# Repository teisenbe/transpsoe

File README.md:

# Transpsoe

This is a Eurorack 1u 22hp module that performs pitch transposition on V/oct signals. Outputs are accurate to within 1.5mV, often better. The panel is designed for Intellijel 1u, but is (untested) compatible with Pulp Logic 1u. Build instructions can be found [here](build_instructions.md). **Note: revs 1 and 2 have not been built yet. Rev 1 but is only minor changes from rev 0, but 2 is more substantial. See the [changelog](CHANGELOG.md) for details.**

## Project Status

- [x] Complete initial CAD work
- [x] SPICE simulations
- [x] Order test board to verify footprints, board alignment, and power connector clearance
- [x] Order and assemble rev 0 PCBs and components
- [ ] Order and assemble rev 2 PCBs and components

## Known issues
- Something on channel 1 produces around -0.5 to -1mV of error in a way that is visible on the +S output (and all channel 2 outputs when summing is enabled). It does not seem to show up on the other outputs, but this might just mean its calibrated out of the voltage refs.

## Controls

Transpsoe has two inputs, 8 outputs, a toggle switch, and a rotary knob. The two rows of jacks corresponds roughly to two channels of operation.

### Inputs

The inputs are identified by white outlines. The jacks are both normed to 0V. Each input is fed to the jacks to their right. The channel summing mechanism can also feed the top input downward.

### Channel summing

The toggle switch can be used to bridge the two channels. If the toggle switch is in the down position, pointing toward the "ADD" label, then the bottom outputs behaves as if the bottom input is increased by the top input and the semitone transposition.

### Semitone transpostion

The rotary knob selects semitone transposition in 12-TET. 0 semitones corresponds to the vertical position, with the extra long radial line.  The number of semitones increases by 1 as you move clockwise. Semitone transposition applies only to the first channel unless channel summing is enabled.

### Outputs

Each output is labeled with an integer representing a number of octaves to shift up the channel's input by. The top channel is also shifted up by the number of semitones selected on the knob.

## Technical details

### Power consumption

- 12V: ~13 mA
- -12V: ~13 mA

### Input/Output voltage limits

All inputs should function fine in the +/- 11V range. All outputs should function fine as long as their expected value is in the +/- 11V range.

### Calibration

1. Apply power to the module.
2. Unplug any patch cables, set the semitone knob to 0, and the summing switch to the off position.
3. Measure the first output on the top. It should be 0V, +/- 1.5mV. This is not adjustable. A substantially different value is indicative of a problem with the circuit.
4. Measure the second output on the top. It should be 1V. Adjust trimpot RV1 to get it as close as possible to 1V.
5. Measure the third and fourth outputs on the top and the first on the bottom. They should be 2V, 3V, and -1V, respectively. They should be pretty close at this point, but if they're not, you can further tune RV1 to minimize the error across the -1V, 1V, 2V, and 3V values.
6. Set the semitone knob to 1 and the summing switch to the off position.
7. Measure the first output on the top. It should be 83.33mV (1/12 mV). Adjust trimpot RV2 to tune as close to 83.33mV as you can, since any error here is going to be multiplied by up to 11.

### Voltage reference

The circuit generates a 4.096V +/- 0.1% reference using a shunt diode. A resistor divider with a trimpot is used to get a 4V reference. -1V, 1V, 2V, and 3V references are generated from the 4V reference.

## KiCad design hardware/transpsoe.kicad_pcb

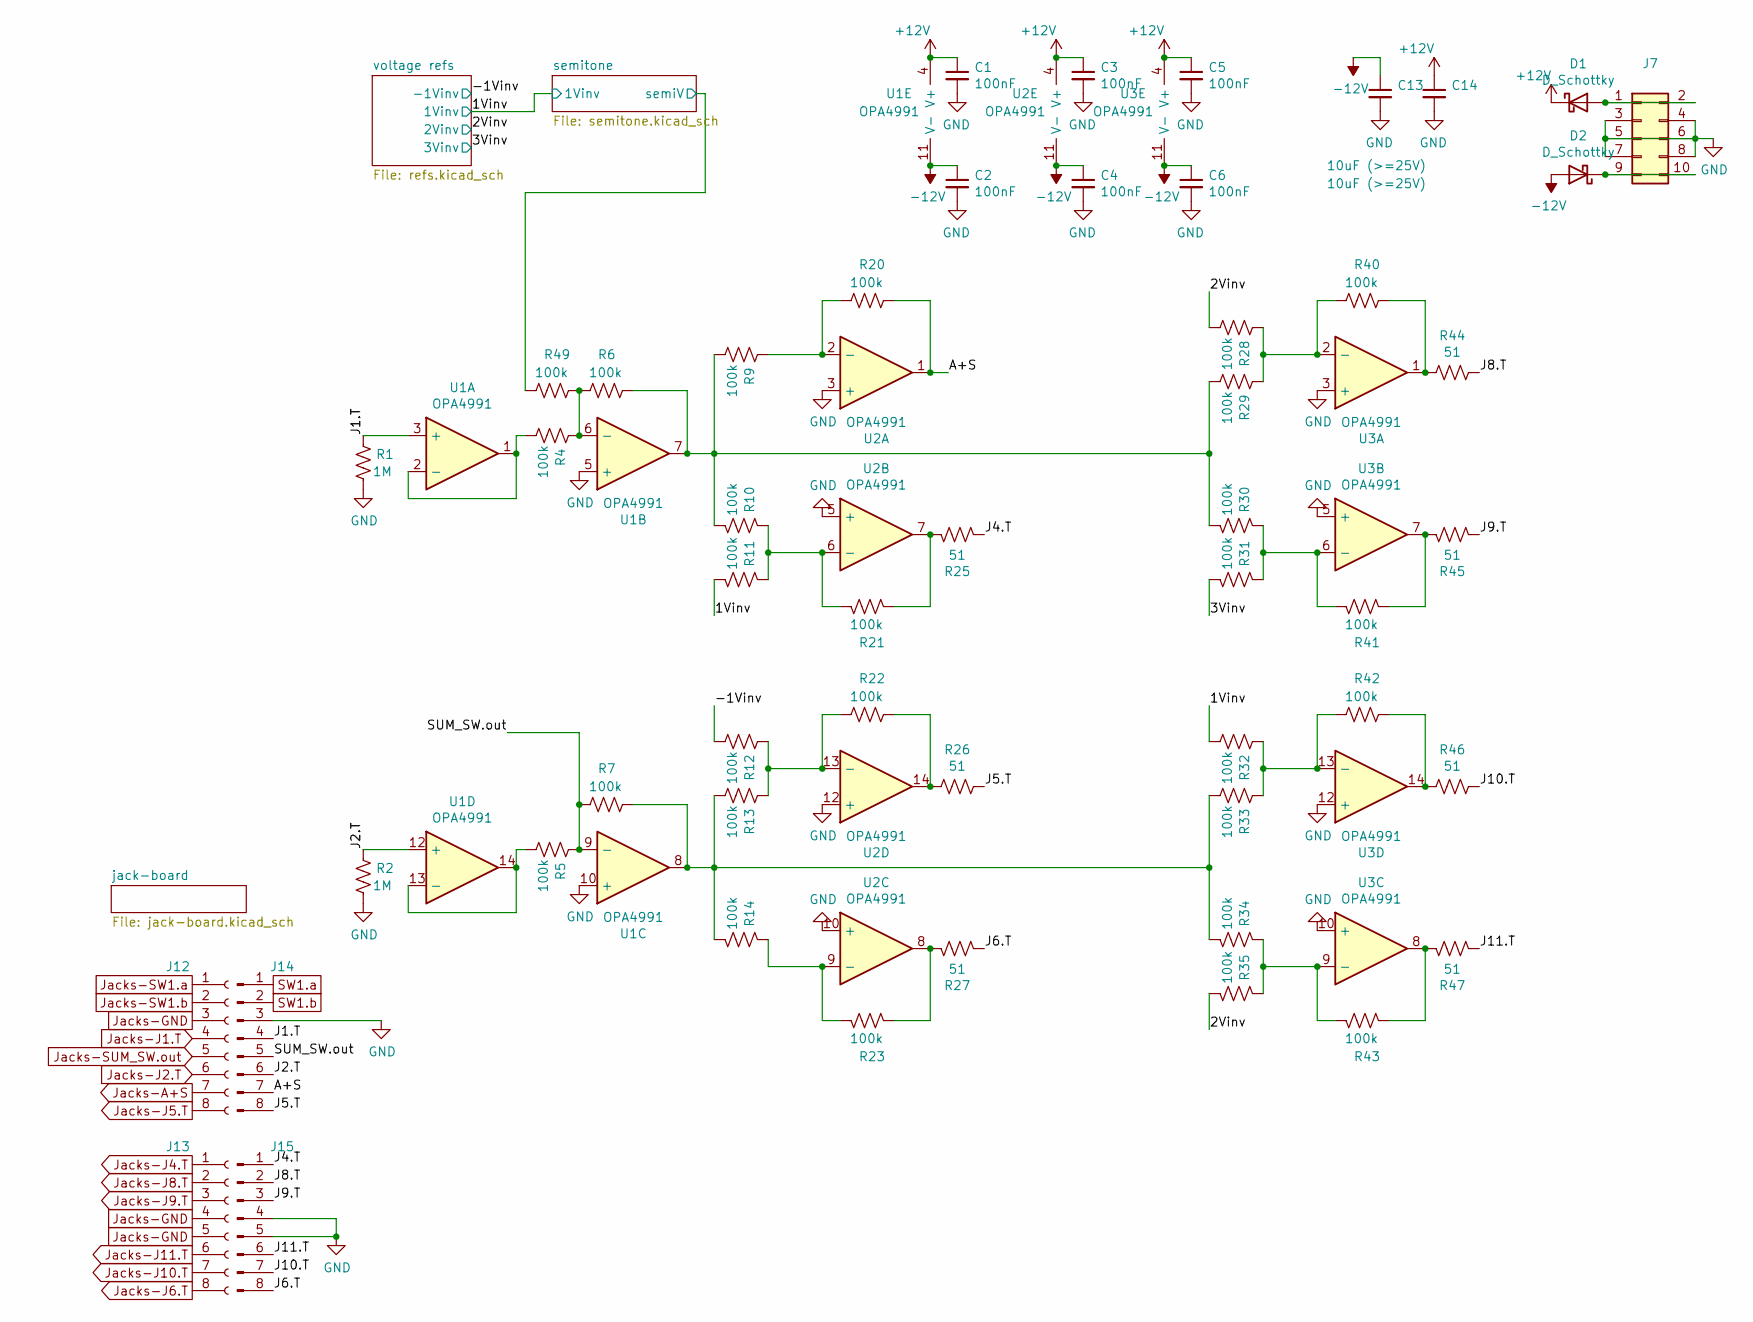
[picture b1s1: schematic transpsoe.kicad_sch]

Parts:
C1, C2, C3, C4, C5, C6: 100nF; C_0603_1608Metric_Pad1.08x0.95mm_HandSolder
C13, C14: 10uF (>=25V); C_0603_1608Metric_Pad1.08x0.95mm_HandSolder
D1, D2: D_Schottky; D_SMA_Handsoldering
J7: Conn_02x05_Odd_Even; PinHeader_2x05_P2.54mm_Vertical
J12, J13: Conn_01x08_Female; SAMTEC_SSM-108-L-SV-LC
J14, J15: Conn_01x08_Male; SAMTEC_TSM-108-01-F-SV-LC
R1, R2: 1M; R_0603_1608Metric_Pad0.98x0.95mm_HandSolder; Tolerance 5%
R4, R5, R6, R7, R9, R10, R11, R12, R13, R14, R20, R21, R22, R23, R28, R29, R30, R31, R32, R33, R34, R35, R40, R41, R42, R43, R49: 100k; R_0603_1608Metric_Pad0.98x0.95mm_HandSolder; Tolerance 0.1%
R25, R26, R27, R44, R45, R46, R47: 51; R_0603_1608Metric_Pad0.98x0.95mm_HandSolder; Tolerance 5%
U1, U2, U3: OPA4991; SOIC-14_3.9x8.7mm_P1.27mm

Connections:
+12V: C1.1, C3.1, C5.1, C14.1, D1.1 (K), U1.4 (V+), U2.4 (V+), U3.4 (V+); also elsewhere on the board
-12V: C2.1, C4.1, C6.1, C13.1, D2.2 (A), U1.11 (V-), U2.11 (V-), U3.11 (V-); also elsewhere on the board
/1Vinv: R11.2, R32.2; also elsewhere on the board
/2Vinv: R28.2, R35.2; also elsewhere on the board
/3Vinv: R31.2; also elsewhere on the board
/-1Vinv: R12.2; also elsewhere on the board
/A+S: J14.7, R20.1, U2.1
/J1.T: J14.4, R1.1, U1.3 (+)
/J2.T: J14.6, R2.1, U1.12 (+)
/J4.T: J15.1, R25.2
/J5.T: J14.8, R26.2
/J6.T: J15.8, R27.2
/J8.T: J15.2, R44.2
/J9.T: J15.3, R45.2
/J10.T: J15.7, R46.2
/J11.T: J15.6, R47.2
/SUM_SW.out: J14.5, R5.1, R7.2, U1.9 (-)
GND: C1.2, C2.2, C3.2, C4.2, C5.2, C6.2, C13.2, C14.2, J7.3, J7.4, J7.5, J7.6, J7.7, J7.8, J14.3, J15.4, J15.5, R1.2, R2.2, U1.5 (+), U1.10 (+), U2.3 (+), U2.5 (+), U2.10 (+), U2.12 (+), U3.3 (+), U3.5 (+), U3.10 (+), U3.12 (+); also elsewhere on the board
Jacks-A+S: J12.7; also elsewhere on the board
Jacks-GND: J12.3, J13.4, J13.5; also elsewhere on the board
Jacks-J1.T: J12.4; also elsewhere on the board
Jacks-J2.T: J12.6; also elsewhere on the board
Jacks-J4.T: J13.1; also elsewhere on the board
Jacks-J5.T: J12.8; also elsewhere on the board
Jacks-J6.T: J13.8; also elsewhere on the board
Jacks-J8.T: J13.2; also elsewhere on the board
Jacks-J9.T: J13.3; also elsewhere on the board
Jacks-J10.T: J13.7; also elsewhere on the board
Jacks-J11.T: J13.6; also elsewhere on the board
Jacks-SUM_SW.out: J12.5; also elsewhere on the board
Jacks-SW1.a: J12.1; also elsewhere on the board
Jacks-SW1.b: J12.2; also elsewhere on the board
unnamed: D1.2 (A), J7.1, J7.2
unnamed: D2.1 (K), J7.9, J7.10
unnamed: R4.1, R6.2, R49.1, U1.6 (-)
unnamed: R4.2, U1.1, U1.2 (-)
unnamed: R5.2, U1.13 (-), U1.14
unnamed: R10.1, R11.1, R21.2, U2.6 (-)
unnamed: R6.1, R9.2, R10.2, R29.2, R30.2, U1.7
unnamed: R12.1, R13.1, R22.2, U2.13 (-)
unnamed: R7.1, R13.2, R14.2, R33.2, R34.2, U1.8
unnamed: R14.1, R23.2, U2.9 (-)
unnamed: R9.1, R20.2, U2.2 (-)
unnamed: R21.1, R25.1, U2.7
unnamed: R22.1, R26.1, U2.14
unnamed: R23.1, R27.1, U2.8
unnamed: R28.1, R29.1, R40.2, U3.2 (-)
unnamed: R30.1, R31.1, R41.2, U3.6 (-)
unnamed: R32.1, R33.1, R42.2, U3.13 (-)
unnamed: R34.1, R35.1, R43.2, U3.9 (-)
unnamed: R40.1, R44.1, U3.1
unnamed: R41.1, R45.1, U3.7
unnamed: R42.1, R46.1, U3.14
unnamed: R43.1, R47.1, U3.8
SW1.a: J14.1; also elsewhere on the board
SW1.b: J14.2, R49.2; also elsewhere on the board

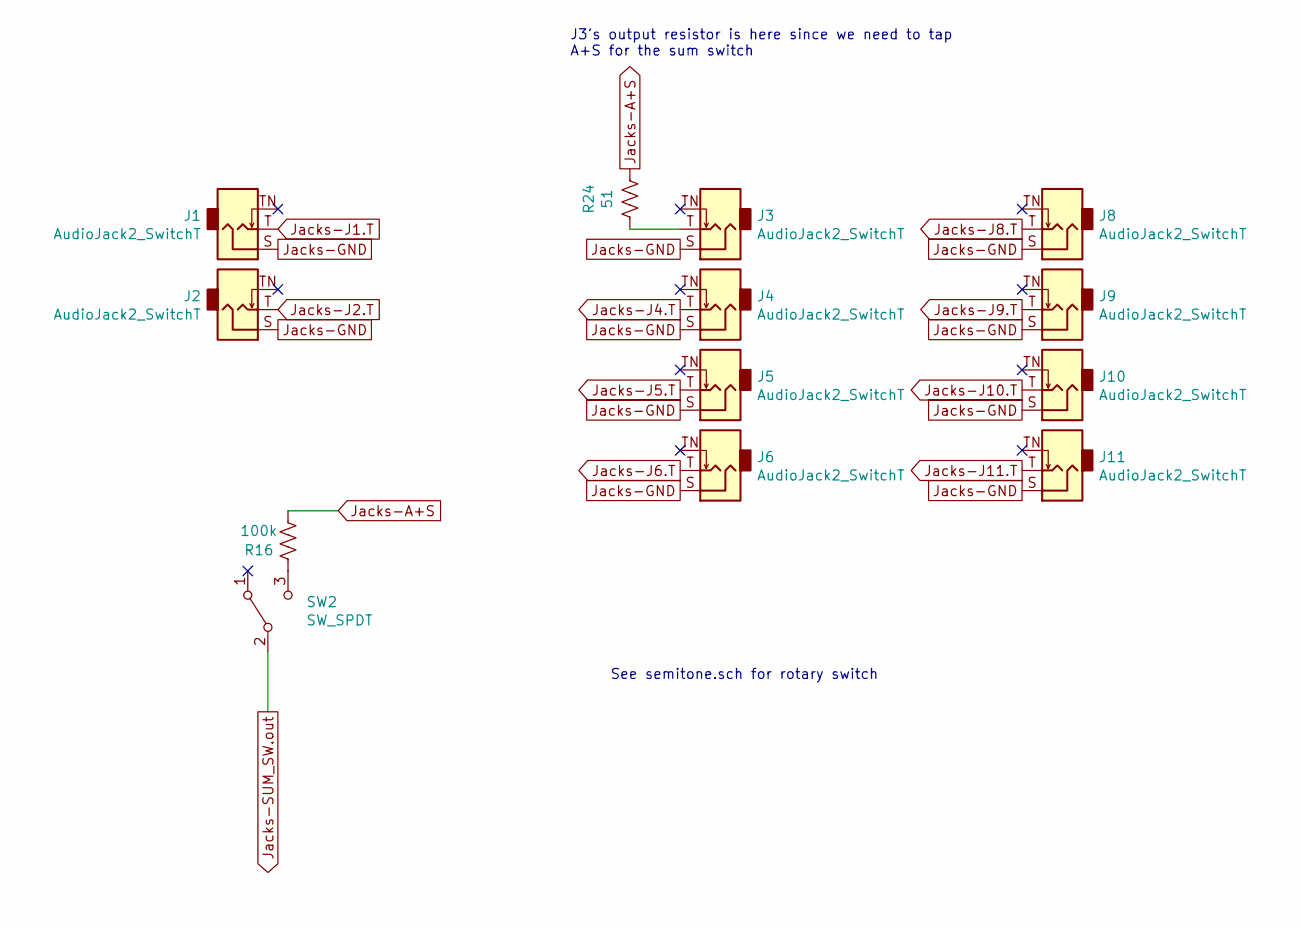
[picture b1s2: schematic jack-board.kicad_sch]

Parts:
J1, J2, J3, J4, J5, J6, J8, J9, J10, J11: AudioJack2_SwitchT; PJ-301BM
R16: 100k; R_0603_1608Metric_Pad0.98x0.95mm_HandSolder; Tolerance 0.1%
R24: 51; R_0603_1608Metric_Pad0.98x0.95mm_HandSolder; Tolerance 5%
SW2: SW_SPDT; BNT11SEA5QE

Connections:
Jacks-A+S: R16.2, R24.2; also elsewhere on the board
Jacks-GND: J1.S, J2.S, J3.S, J4.S, J5.S, J6.S, J8.S, J9.S, J10.S, J11.S; also elsewhere on the board
Jacks-J1.T: J1.T; also elsewhere on the board
Jacks-J2.T: J2.T; also elsewhere on the board
Jacks-J4.T: J4.T; also elsewhere on the board
Jacks-J5.T: J5.T; also elsewhere on the board
Jacks-J6.T: J6.T; also elsewhere on the board
Jacks-J8.T: J8.T; also elsewhere on the board
Jacks-J9.T: J9.T; also elsewhere on the board
Jacks-J10.T: J10.T; also elsewhere on the board
Jacks-J11.T: J11.T; also elsewhere on the board
Jacks-SUM_SW.out: SW2.2 (B); also elsewhere on the board
unnamed: J3.T, R24.1
unnamed: R16.1, SW2.3 (C)

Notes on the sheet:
See semitone.sch for rotary switch
J3's output resistor is here since we need to tap A+S for the sum switch

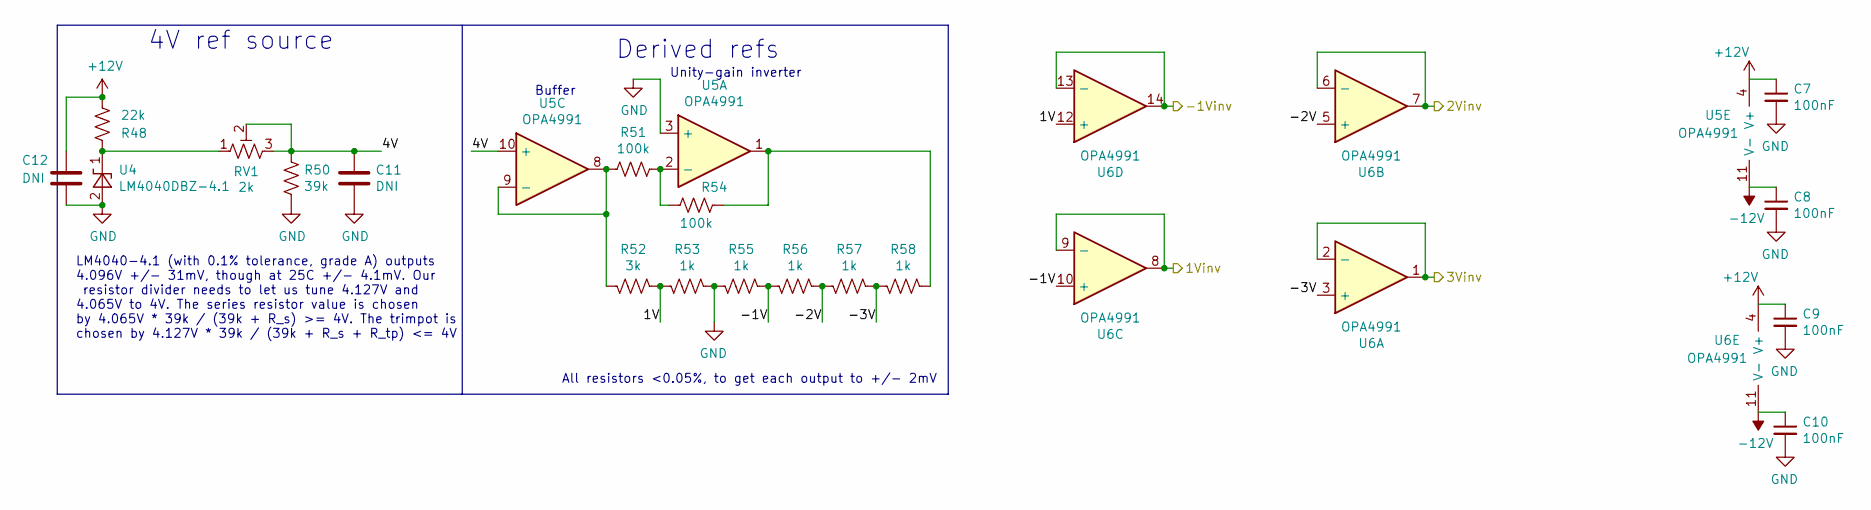
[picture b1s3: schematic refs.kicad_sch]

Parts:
C7, C8, C9, C10: 100nF; C_0603_1608Metric_Pad1.08x0.95mm_HandSolder
C11, C12: DNI; C_0603_1608Metric_Pad1.08x0.95mm_HandSolder
R48: 22k; R_0603_1608Metric_Pad0.98x0.95mm_HandSolder; Tolerance 1%
R50: 39k; R_0603_1608Metric_Pad0.98x0.95mm_HandSolder; Tolerance 1%, but low temp co
R51, R54: 100k; R_0603_1608Metric_Pad0.98x0.95mm_HandSolder; Tolerance 0.1%
R52: 3k; R_0603_1608Metric_Pad0.98x0.95mm_HandSolder; Tolerance 0.05%, low temp co
R53, R55, R56, R57, R58: 1k; R_0603_1608Metric_Pad0.98x0.95mm_HandSolder; Tolerance 0.05%, low temp co
RV1: 2k; Potentiometer_Bourns_3296W_Vertical; Tolerance 10%
U4: LM4040DBZ-4.1; SOT-23; Tolerance 0.1%
U5, U6: OPA4991; SOIC-14_3.9x8.7mm_P1.27mm

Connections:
+12V: C7.1, C9.1, C12.1, R48.1, U5.4 (V+), U6.4 (V+); also elsewhere on the board
-12V: C8.1, C10.1, U5.11 (V-), U6.11 (V-); also elsewhere on the board
/1Vinv: U6.8, U6.9 (-); also elsewhere on the board
/2Vinv: U6.6 (-), U6.7; also elsewhere on the board
/3Vinv: U6.1, U6.2 (-); also elsewhere on the board
/-1Vinv: U6.13 (-), U6.14; also elsewhere on the board
/voltage refs/1V: R52.2, R53.1, U6.12 (+)
/voltage refs/4V: C11.1, R50.1, RV1.2, RV1.3, U5.10 (+)
/voltage refs/-1V: R55.2, R56.1, U6.10 (+)
/voltage refs/-2V: R56.2, R57.1, U6.5 (+)
/voltage refs/-3V: R57.2, R58.1, U6.3 (+)
GND: C7.2, C8.2, C9.2, C10.2, C11.2, C12.2, R50.2, R53.2, R55.1, U4.2 (A), U5.3 (+); also elsewhere on the board
unnamed: R48.2, RV1.1, U4.1 (K)
unnamed: R51.1, R54.2, U5.2 (-)
unnamed: R51.2, R52.1, U5.8, U5.9 (-)
unnamed: R54.1, R58.2, U5.1

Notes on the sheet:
Derived refs
Unity-gain inverter
All resistors <0.05%, to get each output to +/- 2mV
4V ref source
LM4040-4.1 (with 0.1% tolerance, grade A) outputs 4.096V +/- 31mV, though at 25C +/- 4.1mV. Our resistor divider needs to let us tune 4.127V and 4.065V to 4V. The series resistor value is chosen by 4.065V * 39k / (39k + R_s) >= 4V. The trimpot is chosen by 4.127V * 39k / (39k + R_s + R_tp) <= 4V
Buffer

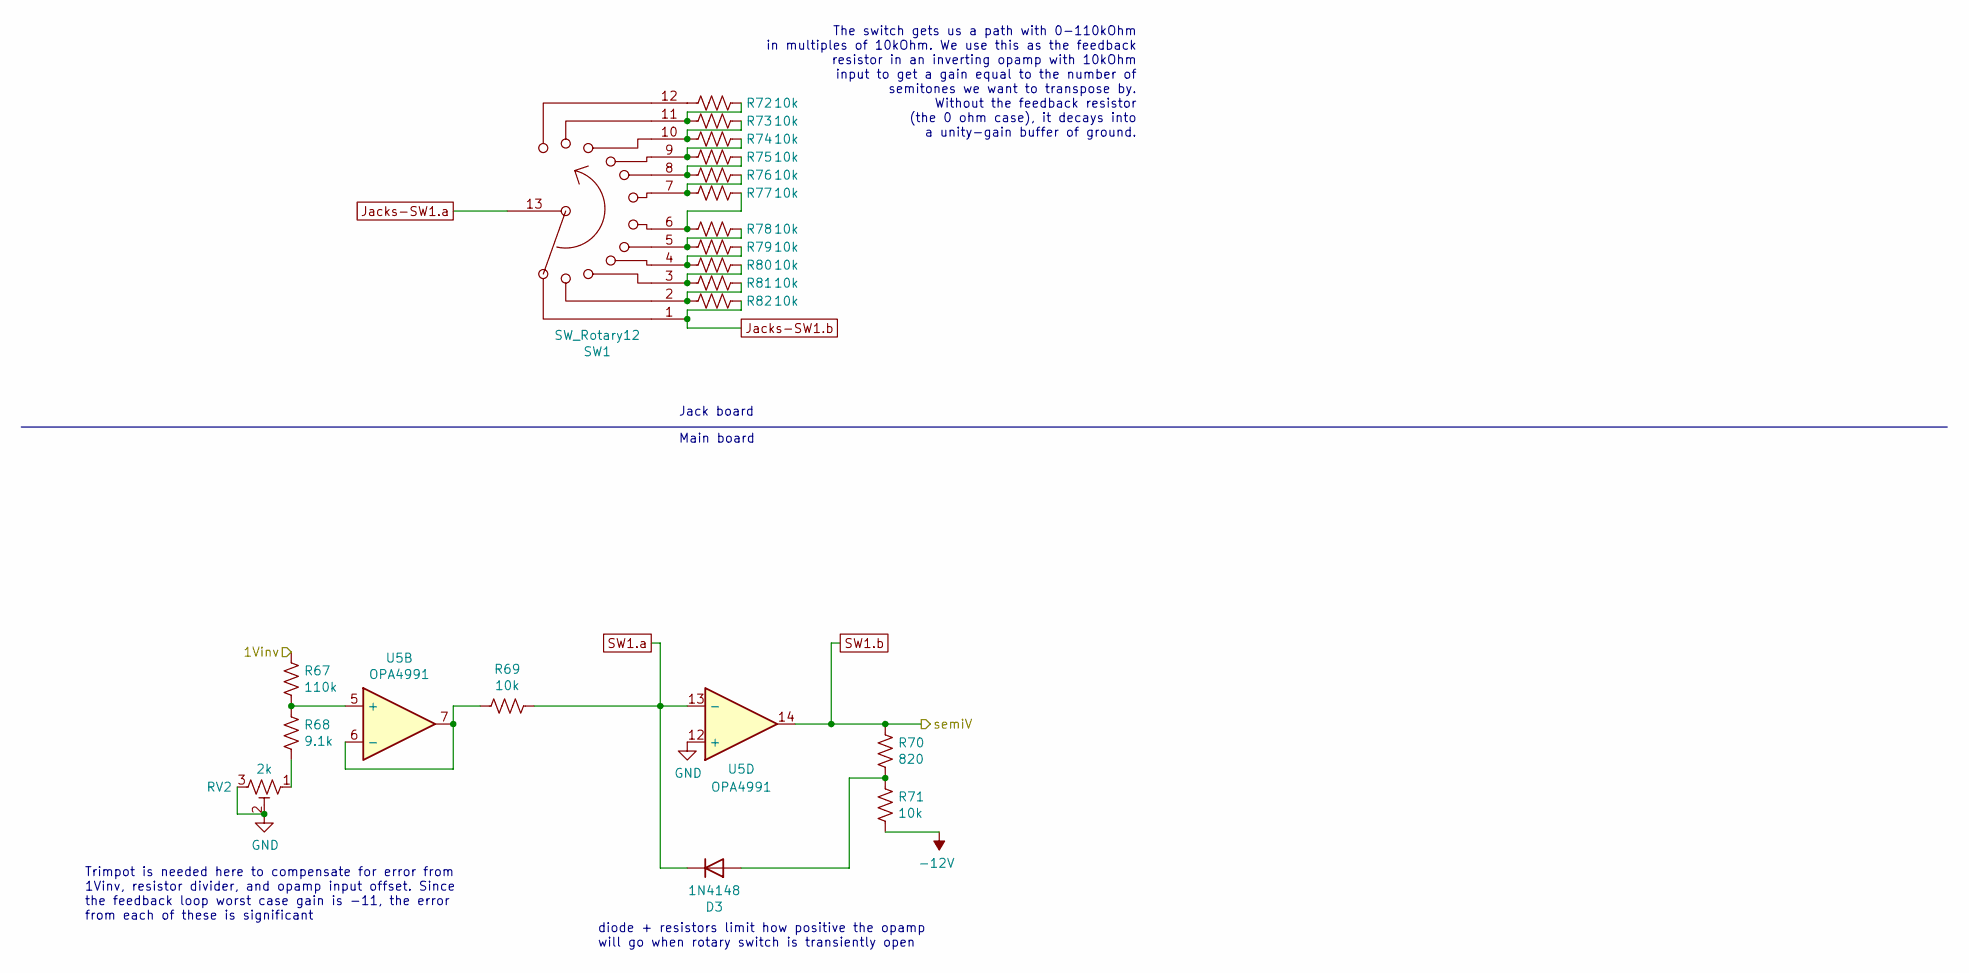
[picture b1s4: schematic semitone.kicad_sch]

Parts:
D3: 1N4148; D_SOD-123
R67: 110k; R_0603_1608Metric_Pad0.98x0.95mm_HandSolder; Tolerance 1%, low temp co
R68: 9.1k; R_0603_1608Metric_Pad0.98x0.95mm_HandSolder; Tolerance 1%
R69, R72, R73, R74, R75, R76, R77, R78, R79, R80, R81, R82: 10k; R_0603_1608Metric_Pad0.98x0.95mm_HandSolder; Tolerance 0.1%
R70: 820; R_0603_1608Metric_Pad0.98x0.95mm_HandSolder; Tolerance 1%
R71: 10k; R_0603_1608Metric_Pad0.98x0.95mm_HandSolder; Tolerance 1%
RV2: 2k; Potentiometer_Bourns_3296W_Vertical; Tolerance 10%
SW1: SW_Rotary12; MC12xxxCxx
U5: OPA4991; SOIC-14_3.9x8.7mm_P1.27mm

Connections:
-12V: R71.2; also elsewhere on the board
/1Vinv: R67.2; also elsewhere on the board
GND: RV2.2, RV2.3, U5.12 (+); also elsewhere on the board
Jacks-SW1.a: SW1.13; also elsewhere on the board
Jacks-SW1.b: R82.2, SW1.1; also elsewhere on the board
unnamed: D3.2 (A), R70.2, R71.1
unnamed: R67.1, R68.2, U5.5 (+)
unnamed: R68.1, RV2.1
unnamed: R69.2, U5.6 (-), U5.7
unnamed: R72.1, SW1.12
unnamed: R72.2, R73.1, SW1.11
unnamed: R73.2, R74.1, SW1.10
unnamed: R74.2, R75.1, SW1.9
unnamed: R75.2, R76.1, SW1.8
unnamed: R76.2, R77.1, SW1.7
unnamed: R77.2, R78.1, SW1.6
unnamed: R78.2, R79.1, SW1.5
unnamed: R79.2, R80.1, SW1.4
unnamed: R80.2, R81.1, SW1.3
unnamed: R81.2, R82.1, SW1.2
SW1.a: D3.1 (K), R69.1, U5.13 (-); also elsewhere on the board
SW1.b: R70.1, U5.14; also elsewhere on the board

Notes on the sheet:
diode + resistors limit how positive the opamp will go when rotary switch is transiently open
Trimpot is needed here to compensate for error from 1Vinv, resistor divider, and opamp input offset. Since the feedback loop worst case gain is -11, the error from each of these is significant
Jack board
Main board
The switch gets us a path with 0-110kOhm in multiples of 10kOhm. We use this as the feedback resistor in an inverting opamp with 10kOhm input to get a gain equal to the number of semitones we want to transpose by. Without the feedback resistor (the 0 ohm case), it decays into a unity-gain buffer of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

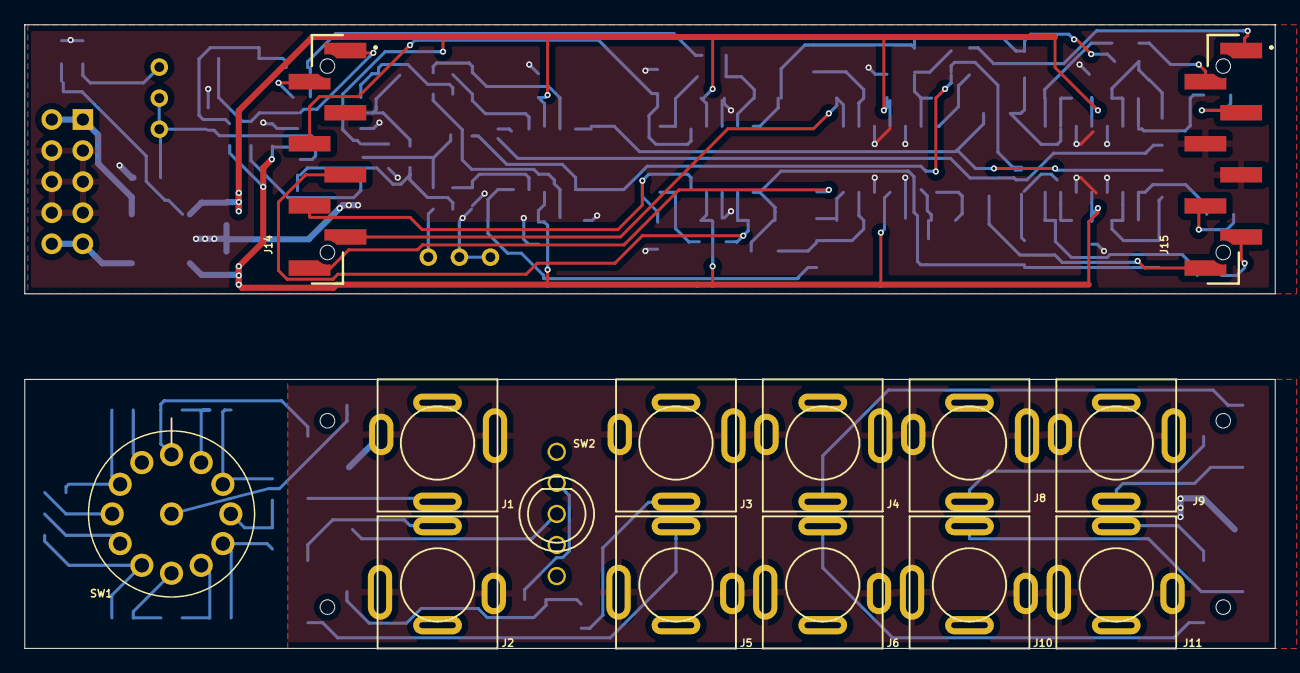
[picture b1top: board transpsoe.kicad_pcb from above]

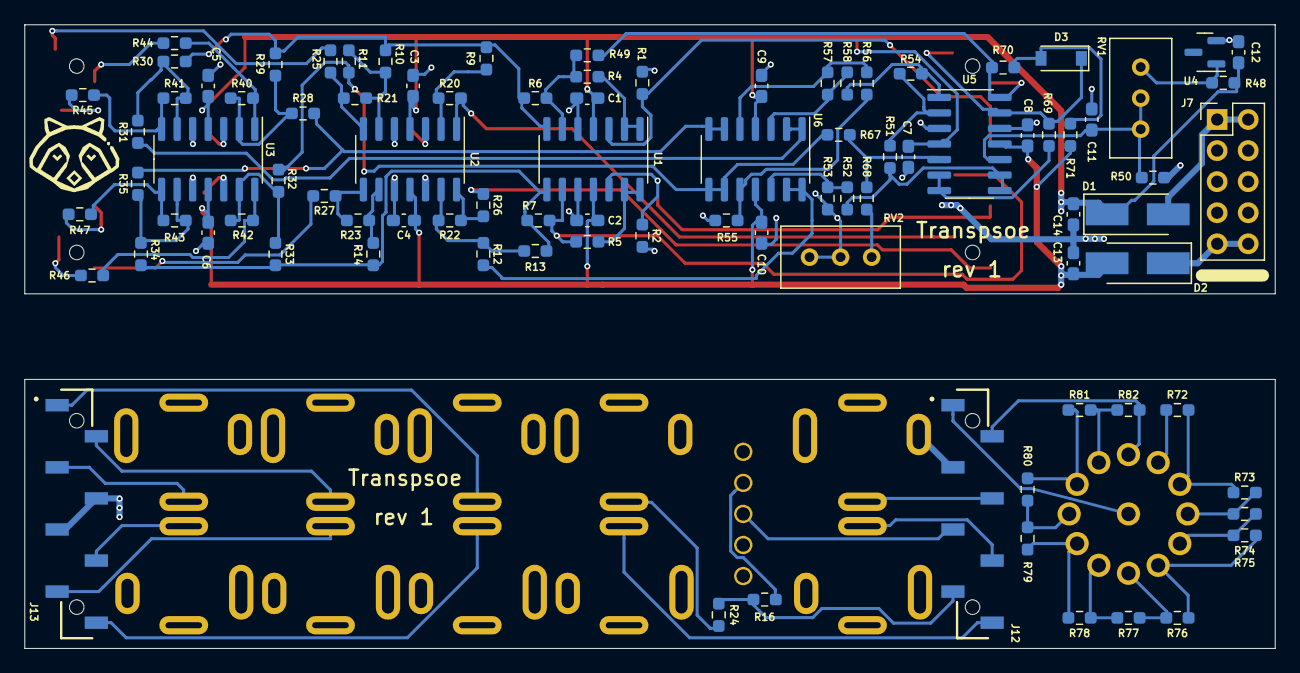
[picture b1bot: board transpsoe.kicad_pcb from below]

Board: 2 copper layers, 102.2 x 51.0 mm, 107 parts (93 on the bottom side), 82 nets.

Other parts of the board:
svg2mod: G***; raccoon-7.5

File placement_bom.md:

# BOM

| Reference | Part |
| --------- | ---- |
|C1|100nF|
|C2|100nF|
|C3|100nF|
|C4|100nF|
|C5|100nF|
|C6|100nF|
|C7|100nF|
|C8|100nF|
|C9|100nF|
|C10|100nF|
|C11|DNI|
|C12|DNI|
|C13|10uF|
|C14|10uF|
|D1|SS14|
|D2|SS14|
|D3|1N4148|
|J1|Audio jack|
|J2|Audio jack|
|J3|Audio jack|
|J4|Audio jack|
|J5|Audio jack|
|J6|Audio jack|
|J7|2x5 pin header|
|J8|Audio jack|
|J9|Audio jack|
|J10|Audio jack|
|J11|Audio jack|
|J12|Samtec SSM-108-L-SV-LC|
|J13|Samtec SSM-108-L-SV-LC|
|J14|Samtec TSM-108-01-F-SV-LC|
|J15|Samtec TSM-108-01-F-SV-LC|
|R1|1M|
|R2|1M|
|R4|100k|
|R5|100k|
|R6|100k|
|R7|100k|
|R9|100k|
|R10|100k|
|R11|100k|
|R12|100k|
|R13|100k|
|R14|100k|
|R16|100k|
|R20|100k|
|R21|100k|
|R22|100k|
|R23|100k|
|R24|51|
|R25|51|
|R26|51|
|R27|51|
|R28|100k|
|R29|100k|
|R30|100k|
|R31|100k|
|R32|100k|
|R33|100k|
|R34|100k|
|R35|100k|
|R40|100k|
|R41|100k|
|R42|100k|
|R43|100k|
|R44|51|
|R45|51|
|R46|51|
|R47|51|
|R48|22k|
|R49|100k|
|R50|39k|
|R51|100k|
|R52|3k|
|R53|1k|
|R54|100k|
|R55|1k|
|R56|1k|
|R57|1k|
|R58|1k|
|R67|110k|
|R68|9.1k|
|R69|10k|
|R70|820|
|R71|10k|
|R72|10k|
|R73|10k|
|R74|10k|
|R75|10k|
|R76|10k|
|R77|10k|
|R78|10k|
|R79|10k|
|R80|10k|
|R81|10k|
|R82|10k|
|RV1|2k|
|RV2|2k|
|SW1|Rotary switch|
|SW2|Toggle switch|
|U1|OPA4991|
|U2|OPA4991|
|U3|OPA4991|
|U4|LM4040|
|U5|OPA4991|
|U6|OPA4991|

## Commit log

2022-01-10 Fix typo in LICENSE.md
2022-01-11 Rotate rotary knob so pin 1 is facing up
    This brings it into alignment with the panel's 0 indicator
2022-01-11 Update rotary switch footprint to make pin 1 point up
2022-01-11 Use different nets for main versus jack board
    This gets rid of the 14 spurious "Unconnected Items" DRCs, and makes
    it more explicit which parts are on which board.
2022-01-11 Remove unnecessary circuit on "up" position of toggle switch
    An open circuit will work just as well as a resistor to ground, with
    fewer parts.
2022-01-11 Remove accidental Notes fields on resistors
2022-01-11 Correct datasheet for rotary switch
2022-01-11 Rework semitone circuit
    - Flip the polarity of the voltage limiter, which accidentally wasn't
    inverted when the subcircuit's output polarity was inverted earlier
    in the design work.
    - Add a trimpot to the semitone voltage reference, to compensate for
    various sources of error
    - Add to the spice model to allow testing the error on the semitone
2022-01-11 Remove extra calibration instruction
2022-01-12 Document part selection suggestions
2022-01-13 Narrow boards by 0.5mm
    It's not a lot, but it gives us a little extra margin in fit-up
2022-01-14 Increase annular ring size on rotary switch
2022-01-15 Update suggested trimpot
2022-01-17 Correct orientation of summing switch
2022-01-17 Call out resistors where low temp co is important
2022-01-19 Change fonts on panel
    Also add a script for fixing up the panel to have
    non-plated thru holes
2022-01-19 Extend panel to 22hp to increase power cable clearance
2022-01-19 Push 3.5mm jacks 0.05mm closer to the edge
    It's a very small nudge, and puts them more at risk of being slightly
    off the board, but increases the tolerances for clearance between
    adjacent jacks. We have ~0.5mm of clearance on the side of the board,
    and this should only eat into at most 0.1mm of it.
2022-01-20 Update renderings
2022-01-30 Fix issues with board and bump rev
    Errata fixed:
    - C2 & R5 refdes were swapped on PCB
    - R44 & R30 refdes were swapped on PCB
    - R46 label off board
    - D2 label off board
    - C11 label on pad
2022-01-30 Fix 3d models and migrate to KiCad6 R/C footprints
2022-01-30 Add build guide
2022-01-30 Minor edits to build instructions
2022-02-05 Update build instructions
2022-02-05 Replace render with photo
2022-02-06 Document I/O voltage limits
2022-02-20 Redesign output circuits
